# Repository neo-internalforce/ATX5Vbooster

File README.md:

# ATX5Vbooster
An interface board enabling powering 5V heavy 90s/00s PC motherboards with modern ATX power supplies (DCDC conversion from 12V input)

Snag list:
LEDs too bright - increase resistor values
Fitting into a motherboard might be problematic - consider an ATX extension lead
Thickness of the DCDC converter gets in the way

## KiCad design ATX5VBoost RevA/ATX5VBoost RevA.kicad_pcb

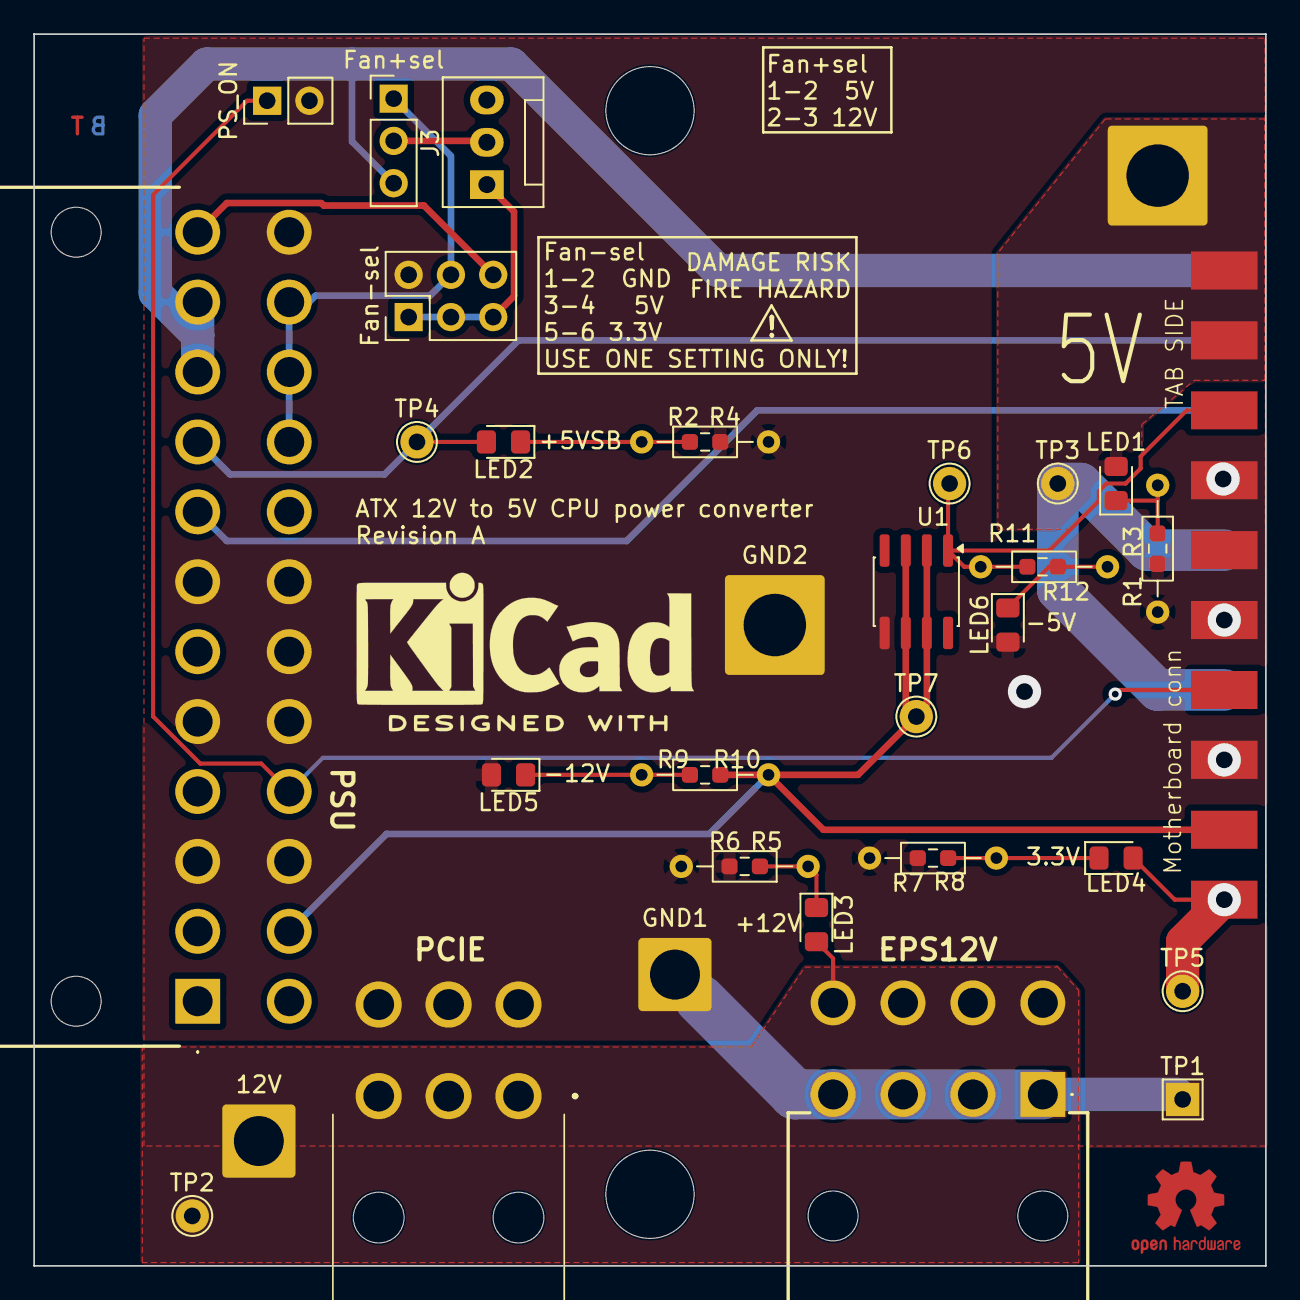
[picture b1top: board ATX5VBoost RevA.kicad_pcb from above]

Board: 2 copper layers, 74.0 x 74.0 mm, 38 parts (0 on the bottom side), 19 nets.

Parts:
5V: Wire; SolderWire-4sqmm_1x01_D3mm_OD6mm
12V: Wire; SolderWire-2.5sqmm_1x01_D2.4mm_OD4.4mm
EPS12V: 1724480008
Fan+sel: Conn_01x03_Pin; PinHeader_1x03_P2.54mm_Vertical
Fan-sel: Conn_02x03_Odd_Even; PinHeader_2x03_P2.54mm_Vertical
GND1: Wire; SolderWire-2.5sqmm_1x01_D2.4mm_OD4.4mm
GND2: Wire; SolderWire-4sqmm_1x01_D3mm_OD6mm
J3: Conn_01x03; FanPinHeader_1x03_P2.54mm_Vertical
LED1, LED2, LED3, LED4, LED5, LED6: LED_Small; LED_0805_2012Metric_Pad1.15x1.40mm_HandSolder
Motherboard conn: ATX20pinEDGE
PCIE: 649006227222
PSU: 649024227222
PS_ON: Conn_01x02; PinHeader_1x02_P2.54mm_Vertical
R1, R2, R12: 240R; R_0603_1608Metric_Pad0.98x0.95mm_HandSolder
R3, R4, R11: 240R; R_Axial_DIN0204_L3.6mm_D1.6mm_P7.62mm_Horizontal
R5, R10: 1k; R_Axial_DIN0204_L3.6mm_D1.6mm_P7.62mm_Horizontal
R6: 1K; R_0603_1608Metric_Pad0.98x0.95mm_HandSolder
R7: 100R; R_Axial_DIN0204_L3.6mm_D1.6mm_P7.62mm_Horizontal
R8: 100R; R_0603_1608Metric_Pad0.98x0.95mm_HandSolder
R9: 1k; R_0603_1608Metric_Pad0.98x0.95mm_HandSolder
TP1: GND; TestPoint_THTPad_2.0x2.0mm_Drill1.0mm
TP2: 12V; TestPoint_THTPad_D2.0mm_Drill1.0mm
TP3: 5V; TestPoint_THTPad_D2.0mm_Drill1.0mm
TP4: +5VSB; TestPoint_THTPad_D2.0mm_Drill1.0mm
TP5: 3.3V; TestPoint_THTPad_D2.0mm_Drill1.0mm
TP6: -5V; TestPoint_THTPad_D2.0mm_Drill1.0mm
TP7: -12V; TestPoint_THTPad_D2.0mm_Drill1.0mm
U1: MC79L05_SO8; SOIC-8_3.9x4.9mm_P1.27mm

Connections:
+3.3V: Fan-sel.6, LED4.2 (A), Motherboard conn.1 (+3.3V), Motherboard conn.2 (+3.3V), Motherboard conn.11 (+3.3V), PSU.1 (3V3), PSU.2 (3V3), PSU.12 (3V3), PSU.13 (3V3), TP5.1 (1_1)
+5V: 5V.1 (Pin_1_1), LED1.2 (A), Motherboard conn.4 (+5V), Motherboard conn.6 (+5V), Motherboard conn.19 (+5V), Motherboard conn.20 (+5V), TP3.1 (1_1)
+12VA: 12V.1 (Pin_1_1), EPS12V.5, EPS12V.6, EPS12V.7, EPS12V.8, LED3.2 (A), PCIE.1, PCIE.2, PCIE.3, TP2.1 (1_1)
GND: EPS12V.1, EPS12V.2, EPS12V.3, EPS12V.4, Fan-sel.2, GND1.1 (Pin_1_1), GND2.1 (Pin_1_1), LED5.2 (A), LED6.2 (A), Motherboard conn.3 (COM), Motherboard conn.5 (COM), Motherboard conn.7 (COM), Motherboard conn.13 (COM), Motherboard conn.15 (COM), Motherboard conn.16 (COM), Motherboard conn.17 (COM), PCIE.4, PCIE.5, PCIE.6, PSU.3 (GND), PSU.5 (GND), PSU.7 (GND), PSU.15 (GND), PSU.17 (GND), PSU.18 (GND), PSU.19 (GND), PSU.24 (GND), PS_ON.2, R1.2, R2.2, R3.2, R4.2, R5.2, R6.2, R7.2, R8.2, TP1.1 (1_1), U1.5 (GND)
unnamed: Fan+sel.1, Fan-sel.4, PSU.21 (5V), PSU.22 (5V), PSU.23 (5V)
unnamed: Fan+sel.2, J3.2
unnamed: Fan+sel.3, Motherboard conn.10 (+12V), PSU.10 (12V), PSU.11 (12V)
unnamed: Fan-sel.1, Fan-sel.3, Fan-sel.5, J3.1
unnamed: LED1.1 (K), R1.1, R3.1
unnamed: LED2.2 (A), Motherboard conn.9 (+5VSB), PSU.9 (+5VSB), TP4.1 (1_1)
unnamed: LED2.1 (K), R2.1, R4.1
unnamed: LED3.1 (K), R5.1, R6.1
unnamed: LED4.1 (K), R7.1, R8.1
unnamed: LED5.1 (K), R9.1, R10.1
unnamed: LED6.1 (K), R11.1, R12.1
unnamed: Motherboard conn.18 (-5V), R11.2, R12.2, TP6.1 (1_1), U1.1 (OUT)
unnamed: Motherboard conn.12 (-12V), PSU.14 (-12V), R9.2, R10.2, TP7.1 (1_1), U1.2 (IN), U1.3 (IN), U1.6 (IN), U1.7 (IN)
unnamed: Motherboard conn.14 (PS_ON#), PSU.16 (PS_ON), PS_ON.1
unnamed: Motherboard conn.8 (PWR_OK), PSU.8 (PGOOD)
